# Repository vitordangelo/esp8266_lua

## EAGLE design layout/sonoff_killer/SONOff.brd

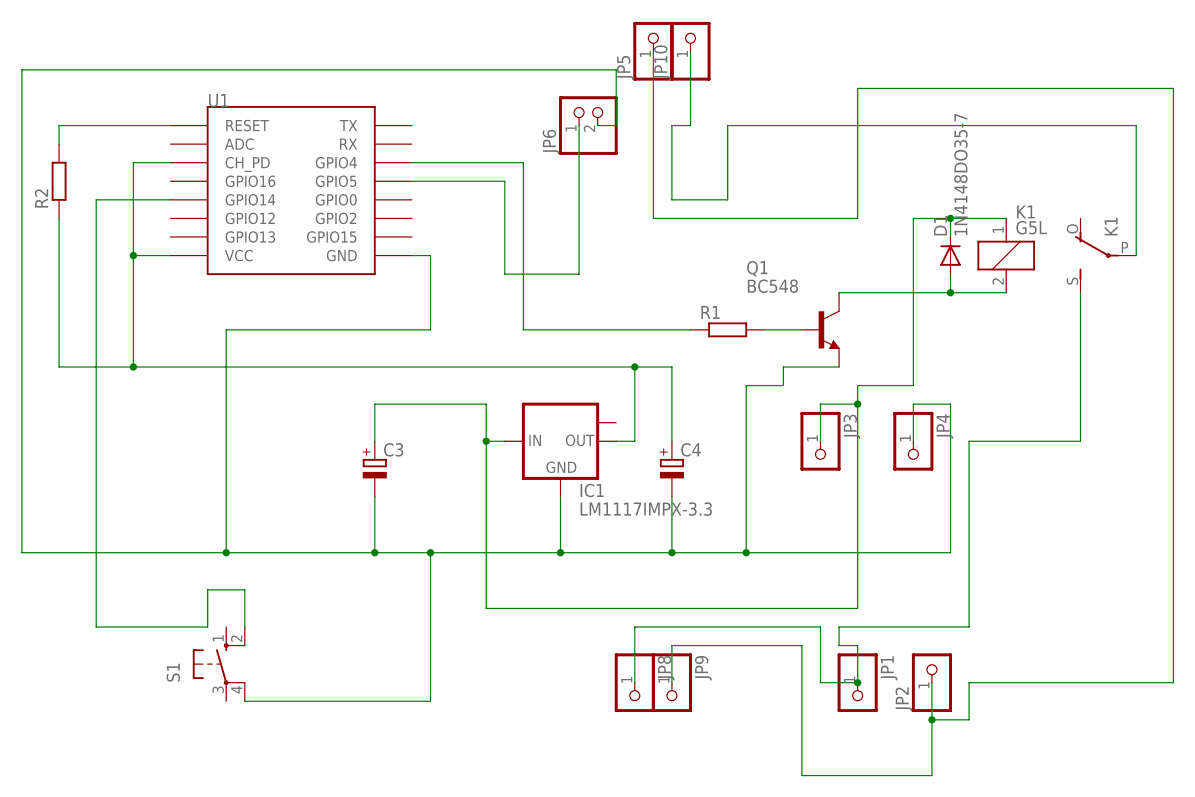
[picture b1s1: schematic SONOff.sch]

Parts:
C3: CPOL-EUE3.5-8; E3,5-8
C4: CPOL-EUE2.5-5; E2,5-5
D1: 1N4148DO35-7; DO35-7
IC1: LM1117IMPX-3.3; SOT223
JP1, JP2, JP3, JP4, JP5, JP8, JP9, JP10: PINHD-1X1; 1X01
JP6: PINHD-1X2; 1X02
K1: G5L; G5LE
Q1: BC548; TO92-EBC
R1, R2: R-EU_0207/10; 0207/10
S1: 10-XX; B3F-10XX
U1: ESP12SMD; ESP12-SMD

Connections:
unnamed: R1.1, U1.GPIO4
unnamed: Q1.B, R1.2
unnamed: D1.A, K1.2, Q1.C
unnamed: C3.+, D1.C, IC1.3 (IN), JP3.1, K1.1
unnamed: JP1.1, JP8.1, K1.S
unnamed: C4.+, IC1.2 (OUT), R2.1, U1.CH_PD, U1.VCC
unnamed: JP2.1, JP5.1, JP9.1
unnamed: JP6.1, U1.GPIO5
unnamed: S1.2 (S1), U1.GPIO14
unnamed: R2.2, U1.RESET
unnamed: C3.-, C4.-, IC1.1 (GND), JP4.1, JP6.2, Q1.E, S1.4 (P1), U1.GND
SAIDA: JP10.1, K1.P

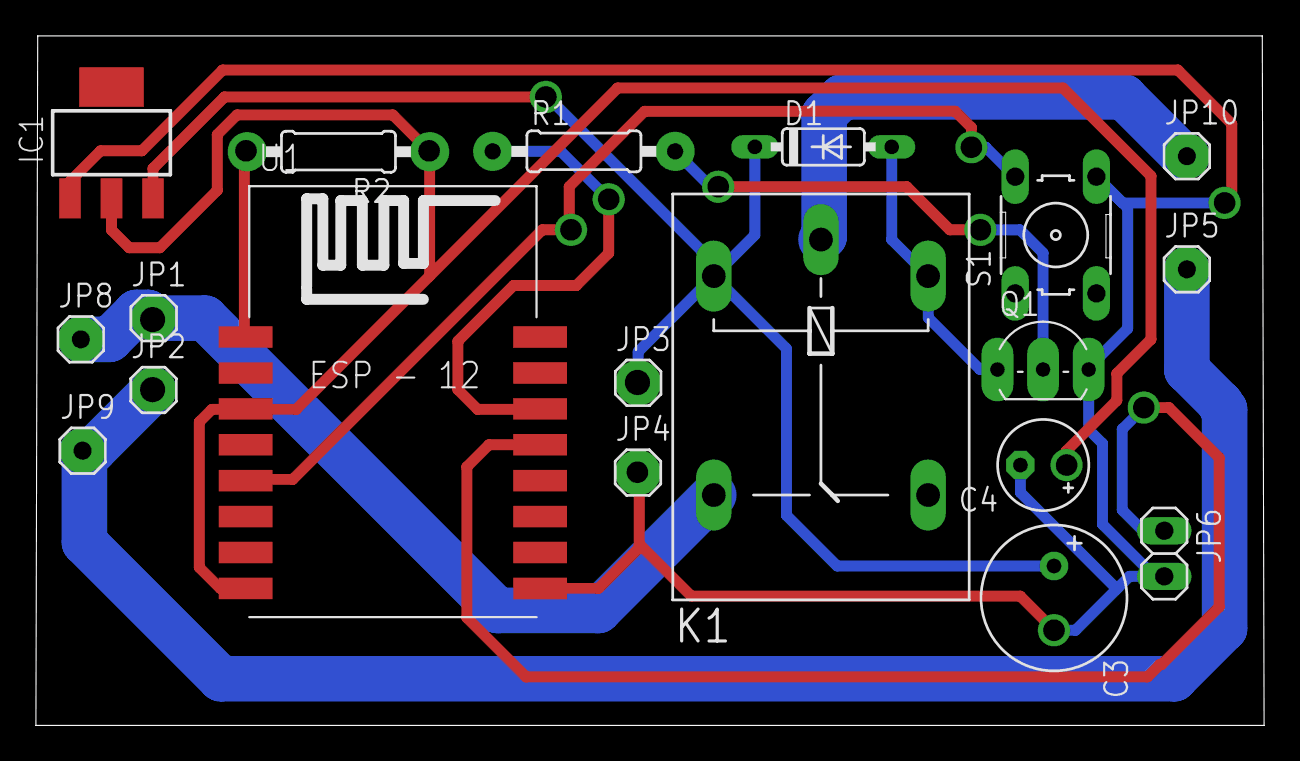
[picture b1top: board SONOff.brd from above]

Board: 2 copper layers, 68.4 x 38.4 mm, 19 parts (0 on the bottom side), 12 nets.

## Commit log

2017-12-13 first
2017-12-14 server
2017-12-20 boot
2017-12-21 bootStation
2018-01-05 firnware
2018-01-22 garage
2018-01-26 garage updated
2018-01-26 module
2018-01-29 module 70%
2018-01-30 module v2
2018-01-30 update module
2018-01-30 firmware
2018-02-01 before relaytimer change
2018-02-02 fix module
2018-02-07 uploader
2018-02-14 sntp
2018-02-15 cron file
2018-02-16 moduleGabriel
2018-02-16 fix retain lwt
2018-02-19 scheduler
2018-02-27 layout
2018-02-28 fienware sonoff
2018-03-12 mqtt tls example
2018-03-12 firnware tls mqtt
2018-03-21 acelerometer and mqtt sll changes
2018-05-15 update hack-sonoff and write-sonoff
2018-05-15 sonoff alarm
2018-05-16 button multi function
2018-05-17 active and desactive alarm
2018-05-18 alarm buzer
2018-06-05 inputWacth
2018-06-05 sonoff alarm arm disarm
2018-06-05 trigger topic
2018-06-05 status trigger
2018-06-06 module sonoff
2018-06-07 strength_wifi
2018-06-08 bug fix to multiple trigger
2018-06-11 wifi signal and identification zone
2018-06-12 update code
2018-06-14 version module cassio
